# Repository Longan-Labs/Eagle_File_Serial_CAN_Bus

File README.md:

Eagle file of [Serial CAN Bus Module](https://www.longan-labs.cc/1030001.html)

Click on [Longan-Labs.cc](https://www.longan-labs.cc/) to get the product you need.

Contact [support@longan-labs.cc](support@longan-labs.cc) if you need help.

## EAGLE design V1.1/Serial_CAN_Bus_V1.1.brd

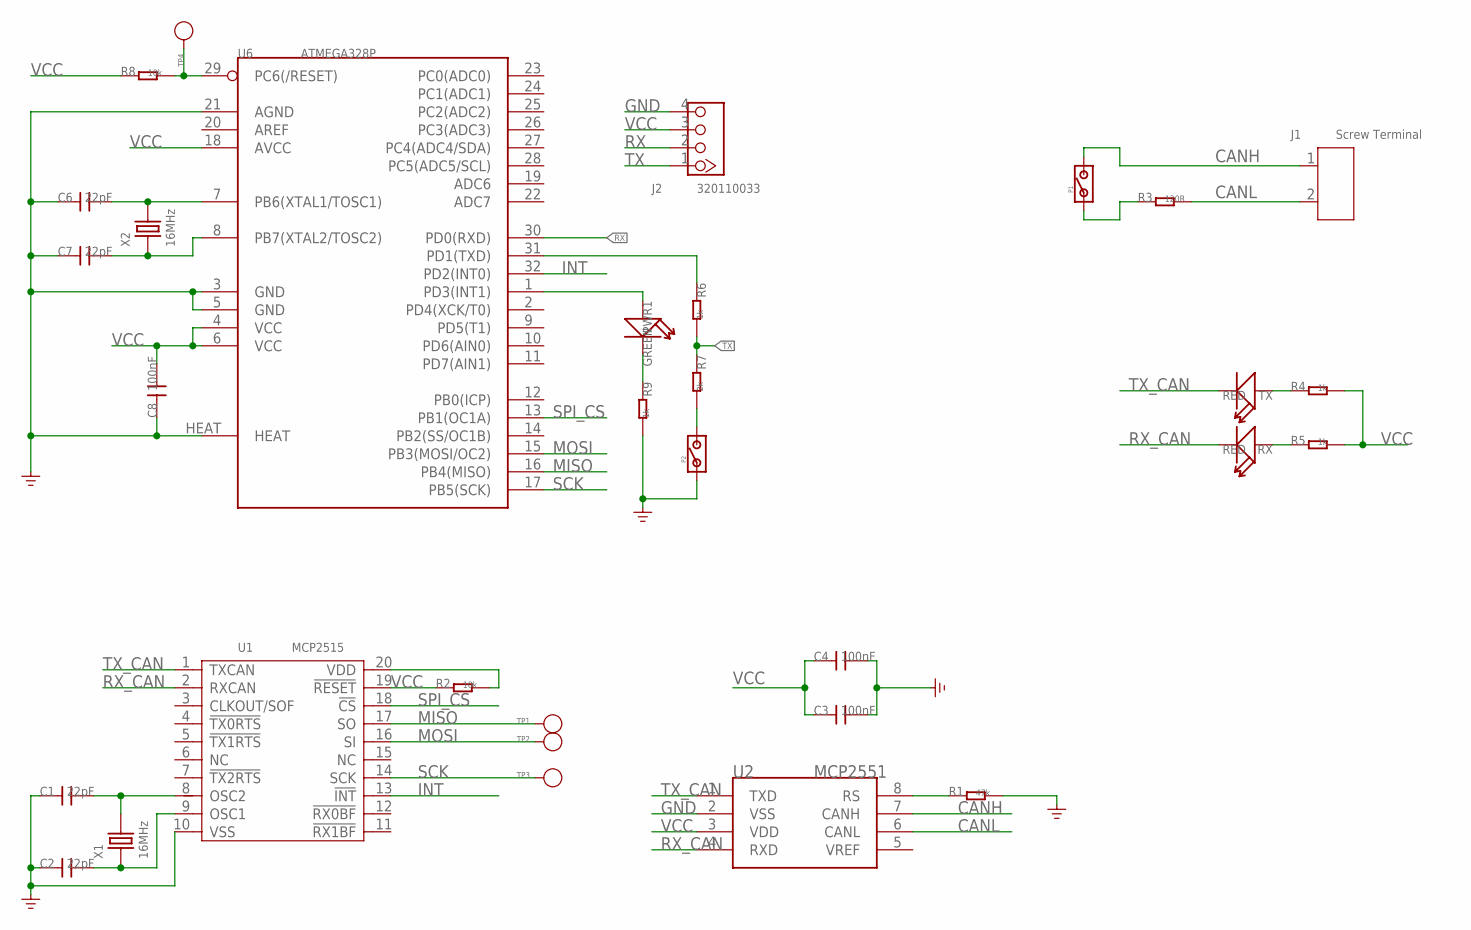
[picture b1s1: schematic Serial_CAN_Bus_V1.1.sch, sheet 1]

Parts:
C1, C2, C6, C7: 22pF; 0603
C3, C4, C8: 100nF; 0603
J1: Screw Terminal; 2P-3.5
J2: 320110033; HW4-2.0
P1, P2: PAD-JUMPER-2P; 2P-SMD-1.78X1.27
PWR1: GREEN; LED-0603
R1: 47k; 0603
R2, R8: 10k; 0603
R3: 120R; 0603
R4, R5, R6, R9: 1k; 0603
R7: 2k; 0603
RX: RED; LED-0603
TP1, TP2, TP3, TP4: PAD-TEST-POINT'4545'; TP_4545
TX: RED; LED-0603
U1: MCP2515; TSSOP20-0.65-6.5X4.4MM
U2: MCP2551; SOIC8-6.0
U6: ATMEGA328P; MLF32X
X1, X2: 16MHz; X2-SMD-5.0X3.2X1.3MM

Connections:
CANH: J1.1, P1.2, U2.7 (CANH)
CANL: J1.2, R3.2, U2.6 (CANL)
GND: C1.1, C2.1, C3.2, C4.2, C6.1, C7.1, C8.1, J2.4, P2.1, R1.2, R9.2, U1.10 (VSS), U2.2 (VSS), U6.3 (GND), U6.5 (GND), U6.21 (AGND), U6.HEAT
INT: U1.13 (!INT), U6.32 (PD2(INT0))
MISO: TP1.T, U1.17 (SO), U6.16 (PB4(MISO))
MOSI: TP2.T, U1.16 (SI), U6.15 (PB3(MOSI/OC2))
unnamed: P1.1, R3.1
unnamed: R4.1, TX.+
unnamed: C6.2, U6.7 (PB6(XTAL1/TOSC1)), X2.2
unnamed: C7.2, U6.8 (PB7(XTAL2/TOSC2)), X2.1
unnamed: R8.2, TP4.T, U6.29 (PC6(/RESET))
unnamed: PWR1.+, U6.1 (PD3(INT1))
unnamed: PWR1.-, R9.1
unnamed: R6.1, U6.31 (PD1(TXD))
unnamed: P2.2, R7.2
unnamed: R5.1, RX.+
unnamed: C1.2, U1.8 (OSC2), X1.2
unnamed: C2.2, U1.9 (OSC1), X1.1
unnamed: R1.1, U2.8 (RS)
RST_N: R2.1, U1.19 (!RESET)
RX: J2.2, U6.30 (PD0(RXD))
RX_CAN: RX.-, U1.2 (RXCAN), U2.4 (RXD)
SCK: TP3.T, U1.14 (SCK), U6.17 (PB5(SCK))
SPI_CS: U1.18 (!CS), U6.13 (PB1(OC1A))
TX: J2.1, R6.2, R7.1
TX_CAN: TX.-, U1.1 (TXCAN), U2.1 (TXD)
VCC: C3.1, C4.1, C8.2, J2.3, R2.2, R4.2, R5.2, R8.1, U1.20 (VDD), U2.3 (VDD), U6.4 (VCC), U6.6 (VCC), U6.18 (AVCC)

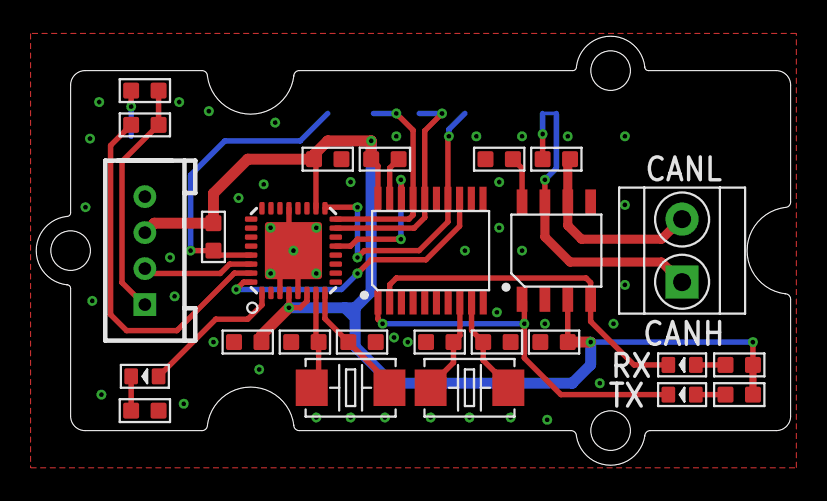
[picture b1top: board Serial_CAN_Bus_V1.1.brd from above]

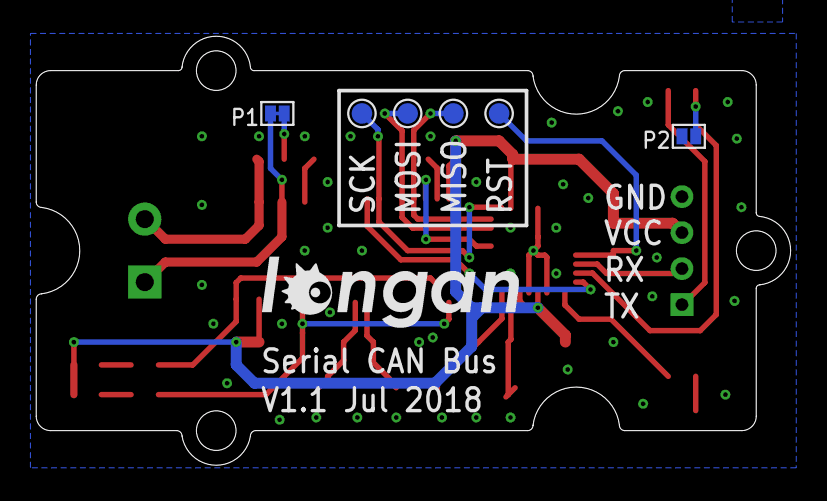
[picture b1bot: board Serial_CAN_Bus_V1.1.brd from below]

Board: 2 copper layers, 41.9 x 23.8 mm, 34 parts (7 on the bottom side), 27 nets.

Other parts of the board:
U3: GROVE-TEST-PLATFORM
U$5: LONGAN-SILK-SMALLER

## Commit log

2022-02-08 add all file
